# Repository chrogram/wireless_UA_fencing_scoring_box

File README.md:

# wireless_UA_fencing_scoring_box

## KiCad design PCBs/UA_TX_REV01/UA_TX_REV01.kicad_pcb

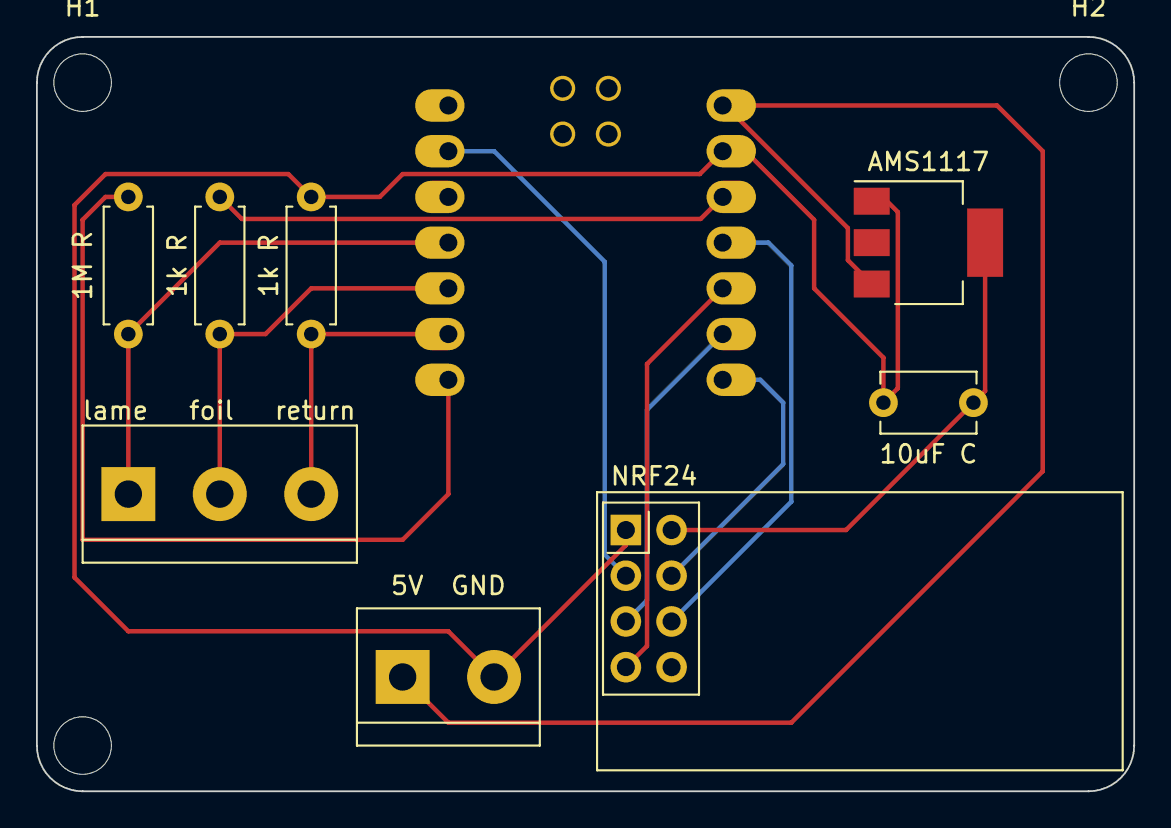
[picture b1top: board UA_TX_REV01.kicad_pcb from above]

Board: 2 copper layers, 61.0 x 41.9 mm, 12 parts (0 on the bottom side), 13 nets.

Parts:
1M R, 1k R, 1k R#2: R; R_Axial_DIN0207_L6.3mm_D2.5mm_P7.62mm_Horizontal
5V  GND: Screw_Terminal_01x02; TerminalBlock_bornier-2_P5.08mm
10uF C: C; C_Disc_D5.1mm_W3.2mm_P5.00mm
AMS1117: AMS1117-3.3; SOT-223-3_TabPin2
H1, H2, H3: MountingHole; MountingHole_3.2mm_M3
NRF24: NRF24L01_Breakout; nRF24L01_Breakout
U1: SeeeduinoXIAO; xiao-tht
lame   foil   return: Screw_Terminal_01x03; TerminalBlock_bornier-3_P5.08mm

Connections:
unnamed: 10uF C.1, AMS1117.2 (VO), NRF24.2 (VCC)
unnamed: 1k R.2, 5V GND.2, 10uF C.2, AMS1117.1 (GND), NRF24.1 (GND), U1.13 (GND)
unnamed: 1M R.2, U1.4 (PA11_A3_D3), lame foil return.1
unnamed: 1k R#2.1, U1.5 (PA8_A4_D4_SDA), lame foil return.2
unnamed: 1k R.1, U1.6 (PA9_A5_D5_SCL), lame foil return.3
unnamed: 5V GND.1, AMS1117.3 (VI), U1.14 (5V)
unnamed: 1M R.1, U1.7 (PB08_A6_D6_TX)
unnamed: 1k R#2.2, U1.12 (3V3)
unnamed: NRF24.4 (~CSN), U1.8 (PB09_A7_D7_RX)
unnamed: NRF24.5 (SCK), U1.9 (PA7_A8_D8_SCK)
unnamed: NRF24.7 (MISO), U1.10 (PA5_A9_D9_MISO)
unnamed: NRF24.6 (MOSI), U1.11 (PA6_A10_D10_MOSI)
unnamed: NRF24.3 (CE), U1.2 (PA4_A1_D1)

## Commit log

2022-10-10 inital commit
2022-10-17 added prototype code
2022-10-17 changed spacing and formatting
2022-10-17 testing channel and datarate
2022-10-21 added network library and implementation:
2022-10-23 data is pipe in near real time
2022-10-23 wrote tx foils
2022-10-27 wireless finally working
2022-11-01 added PCB design files
2022-11-01 changed code to work with PCB
2022-11-02 changed code for ppcb and case
2022-11-14 figured out stuff is broken last revise
2023-06-03 stopped updates
